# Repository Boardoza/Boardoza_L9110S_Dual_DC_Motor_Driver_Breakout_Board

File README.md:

# Boardoza L9110S DC Motor Driver Breakout Board

The **Boardoza L9110S Breakout Board** is a dual-channel DC motor driver board built around the **L9110S motor driver IC.** It integrates a two-channel push-pull power amplifier in a compact breakout form, enabling bidirectional control of two DC motors through simple logic-level inputs.

The board supports **TTL / CMOS compatible control signals** and features low output saturation voltage along with integrated clamp diodes for inductive load protection. These characteristics make it suitable for low-voltage motor control in **embedded systems, including robotics platforms, educational development boards, small automation projects, and basic stepper motor driving applications** where direct GPIO-based motor control is required.

## [Click here to purchase!](https://www.ozdisan.com/p/arduino-sensorleri-ve-modulleri-613/ozd-arduino-l9110s-motor-driver-603181)
| Front Side | Back Side |
| :---: | :---: |
|  |  |

---

## Key Features

- **Dual-Channel DC Motor Driver:** Allows independent forward and reverse control of two DC motors.
- **Wide Operating Voltage Range:** Supports motor supply voltages from **2.5 V to 12 V**.
- **High Current Capability:** Delivers up to **750–800 mA continuous current per channel** with peak currents up to **1.5 -2 A**.
- **TTL / CMOS Compatible Inputs:** Can be directly interfaced with microcontrollers and CPUs without additional level shifting.
- **Low Output Saturation Voltage:** Improves efficiency and reduces power loss during motor operation.
- **Built-in Protection Diodes:** Integrated clamp diodes protect against reverse currents from inductive loads.
- **Low Quiescent Current:** Suitable for power-sensitive and battery-operated applications.

---

## Technical Specifications

**Model:** L9110S  
**Manufacturer:** Boardoza  
**Manufacturer IC:** Generic / Multiple vendors    
**Board Type:** Dual Channel DC Motor Driver Breakout Board  
**Input Voltage Range:** 2.5 V – 12 V  
**Output Current:** 750–800 mA continuous per channel  
**Peak Current:** Up to 1.5 A  
**Logic Level Compatibility:** TTL / CMOS  
**Motor Channels:** 2 (Independent control)  
**Supported Loads:** DC motors, stepper motors, relays, inductive loads  
**Power Input Type:** 2-pin 2.50 mm connector / 2.50 mm pin header  
**Control Interface:** Direct GPIO control (A/B inputs per channel)  
**Operating Temperature:** 0 °C to +80 °C  
**Board Dimensions:** 20 mm × 40 mm

---

## Electrical Characteristics

| Symbol | Parameter            | Min  | Typical | Max  | Unit |
|:-----:|----------------------|:----:|:-------:|:----:|:----:|
| VCC   | Supply Voltage       | 2.5  | 6       | 12   | V    |
| Idd   | Quiescent Current    | —    | 0       | 2    | µA   |
| Iin   | Operating Current    | 200  | 350     | 500  | µA   |
| IC    | Continuous Current   | 750  | 800     | 850  | mA   |
| IMax  | Peak Current         | —    | 1500    | 2000 | mA   |

---

## Logical Control Table – Channel 1 (M1)

| M1_A | M1_B | A | B |
|:----:|:----:|:-:|:-:|
| H    | L    | H | L |
| L    | H    | L | H |
| L    | L    | L | L |
| H    | H    | L | L |

---

## Logical Control Table – Channel 2 (M2)

| M2_A | M2_B | A | B |
|:----:|:----:|:-:|:-:|
| H    | L    | H | L |
| L    | H    | L | H |
| L    | L    | L | L |
| H    | H    | L | L |

## Notes on Logic Levels

- **H (High):** Logic high level (TTL / CMOS compatible)
- **L (Low):** Logic low level  
- Motor direction is determined by the relative logic state of A and B inputs.
- Applying the same logic level to both inputs results in braking behavior.

---

## Board Pinout

### ( J1 ) Control & Power Connector

| Pin Number | Pin Name | Description |
| --- | --- | --- |
| 1 | VCC | Motor voltage positive input |
| 2 | M2_B | Channel 2 control input B |
| 3 | M2_A | Channel 2 control input A |
| 4 | M1_B | Channel 1 control input B |
| 5 | M1_A | Channel 1 control input A |
| 6 | GND | Ground |

### ( J4 ) Control & Power Connector (Parallel to J1)

| Pin Number | Pin Name | Description |
| --- | --- | --- |
| 1 | VCC | Motor voltage positive input |
| 2 | M2_B | Channel 2 control input B |
| 3 | M2_A | Channel 2 control input A |
| 4 | M1_B | Channel 1 control input B |
| 5 | M1_A | Channel 1 control input A |
| 6 | GND | Ground |

### ( J2 ) Motor Output – Channel 1 (M1)

| Pin Number | Pin Name | Description |
| --- | --- | --- |
| 1 | B | Motor output B (Channel 1) |
| 2 | A | Motor output A (Channel 1) |

### ( J3 ) Motor Output – Channel 2 (M2)

| Pin Number | Pin Name | Description |
| --- | --- | --- |
| 1 | B | Motor output B (Channel 2) |
| 2 | A | Motor output A (Channel 2) |

---

## Board Dimensions

---

## Step Files

[Boardoza L9110S.step](./assets/L9110S%20Step.step)

---

## Datasheet

[L9110S Datasheet](./assets/L9110S%20Datasheet.pdf)

---

## Version History

- v1.0 – Initial release

---

## Support

- For questions or technical support, please contact **support@boardoza.com**

---

## **License**

This repository contains both hardware and software components:

### **Hardware Design**

[![CC BY-SA 4.0][cc-by-sa-shield]][cc-by-sa]

All hardware design files are licensed under [Creative Commons Attribution-ShareAlike 4.0 International License][cc-by-sa].

[cc-by-sa]: http://creativecommons.org/licenses/by-sa/4.0/
[cc-by-sa-shield]: https://img.shields.io/badge/License-CC%20BY--SA%204.0-lightgrey.svg

### **Software/Firmware**

[![BSD-3-Clause][bsd-shield]][bsd]

All software and firmware are licensed under [BSD 3-Clause License][bsd].

[bsd]: https://opensource.org/licenses/BSD-3-Clause
[bsd-shield]: https://img.shields.io/badge/License-BSD%203--Clause-blue.svg

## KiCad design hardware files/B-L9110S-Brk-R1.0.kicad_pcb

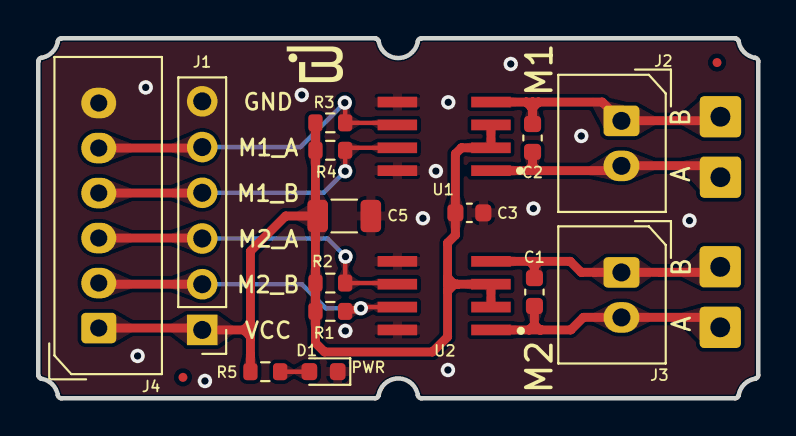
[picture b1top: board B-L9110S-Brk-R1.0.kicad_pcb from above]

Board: 2 copper layers, 40.0 x 20.0 mm, 20 parts (0 on the bottom side), 11 nets.

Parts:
C1, C2, C3: 100nF; C_0603_1608Metric
C5: 10uF; C_1206_3216Metric
D1: LED RED; LED_0603_1608Metric
H1, H2, H3, H4: MountingHole_Pad; SolderWire-0.5sqmm_1x01_D0.9mm_OD2.3mm
J1: Conn_01x06_Pin; PinHeader_1x06_P2.54mm_Vertical
J2, J3: 2317-02; 2317-02S_1x02_P2.50mm_Vertical
J4: CONN_06FEMALE_LOCK; 2317-06S_1x06_P2.50mm_Vertical
R1, R2, R3, R4, R5: 10K; R_0603_1608Metric
U1: L9110
U2: B; L9110

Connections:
GND: C3.2, C5.2, D1.1 (K), J1.6, J4.6, U1.5 (GND@2), U1.8 (GND@1), U2.5 (GND@2), U2.8 (GND@1)
unnamed: D1.2 (A), R5.2
unnamed: J1.2, J4.2, R1.2, U2.7 (IB)
unnamed: J1.3, J4.3, R2.2, U2.6 (IA)
unnamed: J1.4, J4.4, R4.2, U1.7 (IB)
unnamed: J1.5, J4.5, R3.2, U1.6 (IA)
unnamed: C2.2, H4.1, J2.1, U1.4 (OB)
unnamed: C2.1, H3.1, J2.2, U1.1 (OA)
unnamed: C1.2, H2.1, J3.1, U2.4 (OB)
unnamed: C1.1, H1.1, J3.2, U2.1 (OA)
VCC: C3.1, C5.1, J1.1, J4.1, R1.1, R2.1, R3.1, R4.1, R5.1, U1.2 (VCC@1), U1.3 (VCC@2), U2.2 (VCC@1), U2.3 (VCC@2)
